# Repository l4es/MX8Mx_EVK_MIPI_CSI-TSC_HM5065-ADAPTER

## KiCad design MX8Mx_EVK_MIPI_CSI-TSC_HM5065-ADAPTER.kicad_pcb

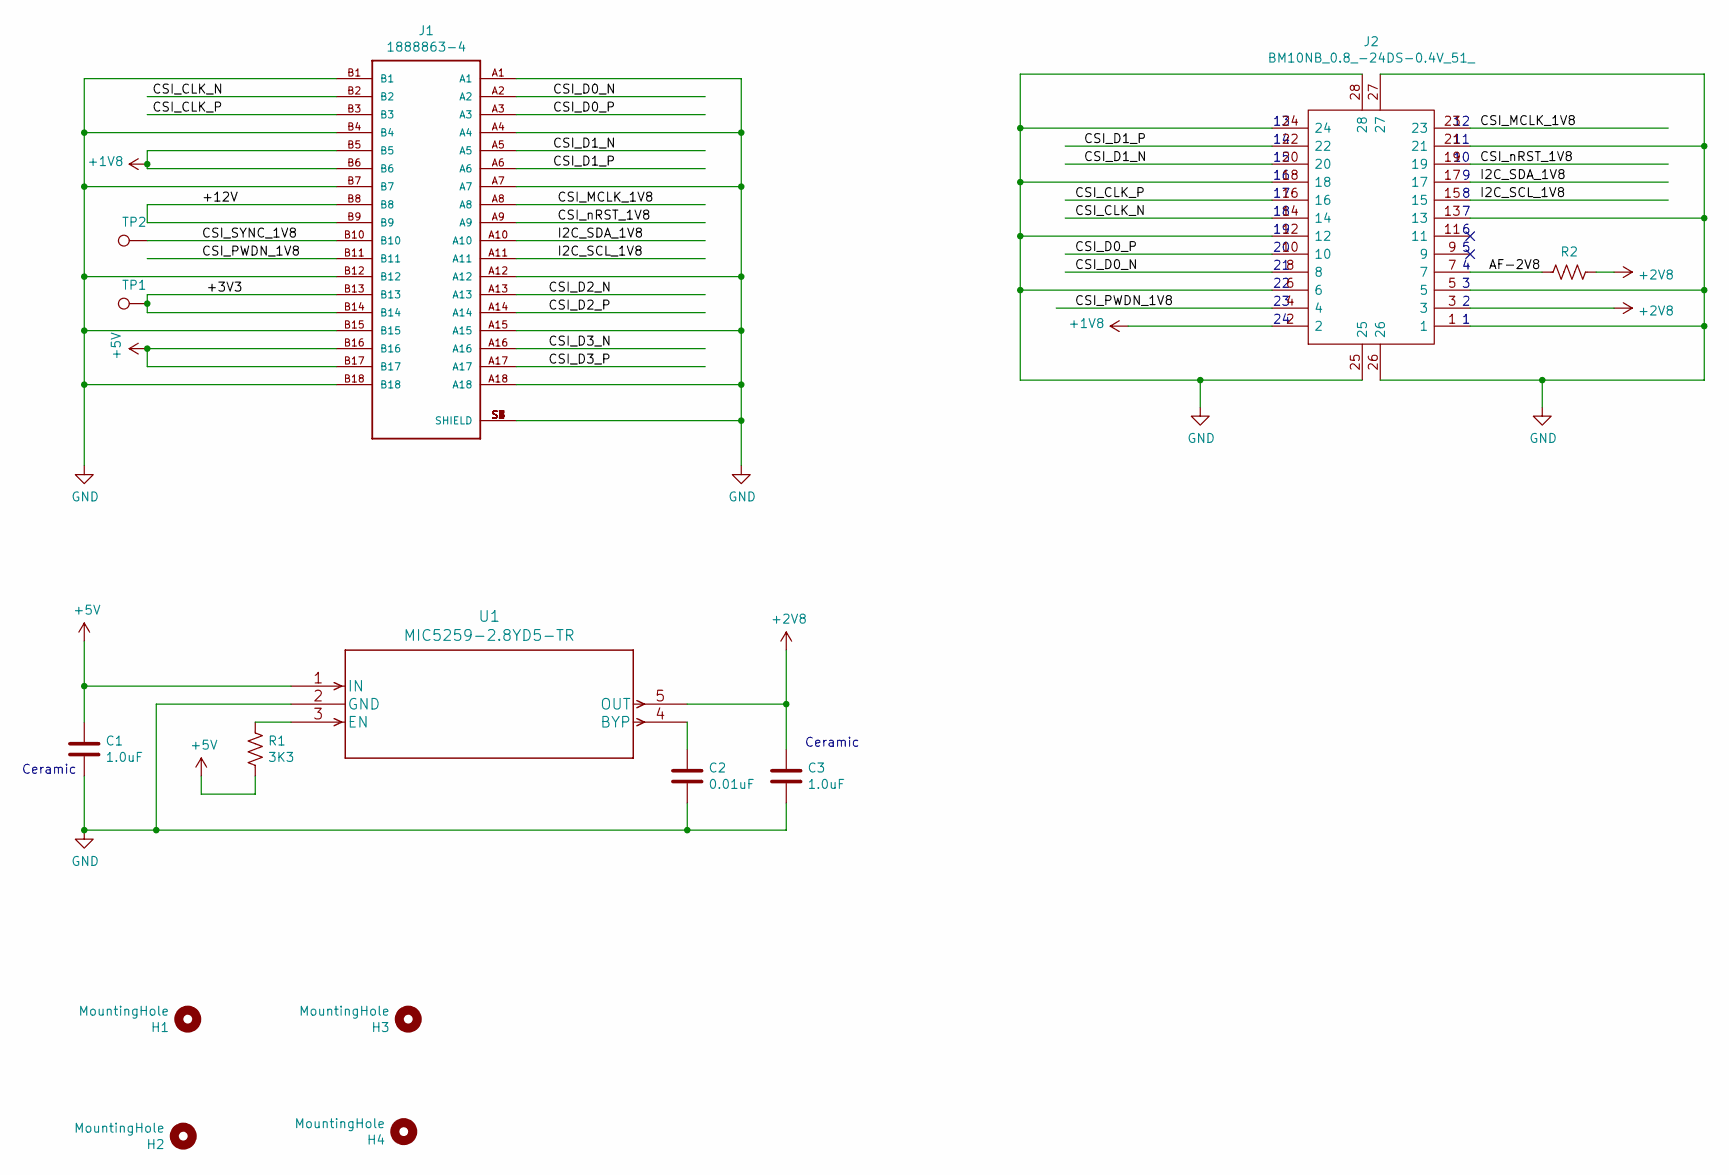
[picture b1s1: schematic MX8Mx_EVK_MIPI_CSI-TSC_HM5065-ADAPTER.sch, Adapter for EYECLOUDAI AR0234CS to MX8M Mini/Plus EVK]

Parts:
C1, C3: 1.0uF; C_0603_1608Metric_Pad1.08x0.95mm_HandSolder
C2: 0.01uF; C_0603_1608Metric_Pad1.08x0.95mm_HandSolder
H1, H2, H3, H4: MountingHole; MountingHole_2.2mm_M2_Pad
J1: 1888863-4; TE_1888863-4
J2: BM10NB_0.8_-24DS-0.4V_51_; BM10NB0824DS04V51; Manufacturer_Part_Number BM10NB(0.8)-24DS-0.4V(51); Mouser Part Number 798-BM10NB0824DS4V51
R1: 3K3; R_0603_1608Metric_Pad0.98x0.95mm_HandSolder
R2: 0; R_0805_2012Metric_Pad1.20x1.40mm_HandSolder
TP1, TP2: TestPoint; TestPoint_Pad_D1.0mm
U1: MIC5259-2.8YD5-TR

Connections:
+1V8: J1.B5, J1.B6, J2.2
+2V8: C3.1, J2.3, R2.2, U1.5 (OUT)
+5V: C1.1, J1.B16, J1.B17, R1.1, U1.1 (IN)
/+3V3: J1.B13, J1.B14, TP1.1
/+12V: J1.B8, J1.B9
/AF-2V8: J2.7, R2.1
/CSI_CLK_N: J1.B2, J2.14
/CSI_CLK_P: J1.B3, J2.16
/CSI_D0_N: J1.A2, J2.8
/CSI_D0_P: J1.A3, J2.10
/CSI_D1_N: J1.A5, J2.20
/CSI_D1_P: J1.A6, J2.22
/CSI_D2_N: J1.A13
/CSI_D2_P: J1.A14
/CSI_D3_N: J1.A16
/CSI_D3_P: J1.A17
/CSI_MCLK_1V8: J1.A8, J2.23
/CSI_PWDN_1V8: J1.B11, J2.4
/CSI_SYNC_1V8: J1.B10, TP2.1
/CSI_nRST_1V8: J1.A9, J2.19
/I2C_SCL_1V8: J1.A11, J2.15
/I2C_SDA_1V8: J1.A10, J2.17
GND: C1.2, C2.2, C3.2, J1.A1, J1.A4, J1.A7, J1.A12, J1.A15, J1.A18, J1.B1, J1.B4, J1.B7, J1.B12, J1.B15, J1.B18, J1.S1 (SHIELD), J1.S2 (SHIELD), J1.S3 (SHIELD), J1.S4 (SHIELD), J1.S5 (SHIELD), J1.S6 (SHIELD), J1.S7 (SHIELD), J1.S8 (SHIELD), J2.1, J2.5, J2.6, J2.12, J2.13, J2.18, J2.21, J2.24, J2.25, J2.26, J2.27, J2.28, U1.2 (GND)
unnamed: C2.1, U1.4 (BYP)
unnamed: R1.2, U1.3 (EN)

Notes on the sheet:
Ceramic

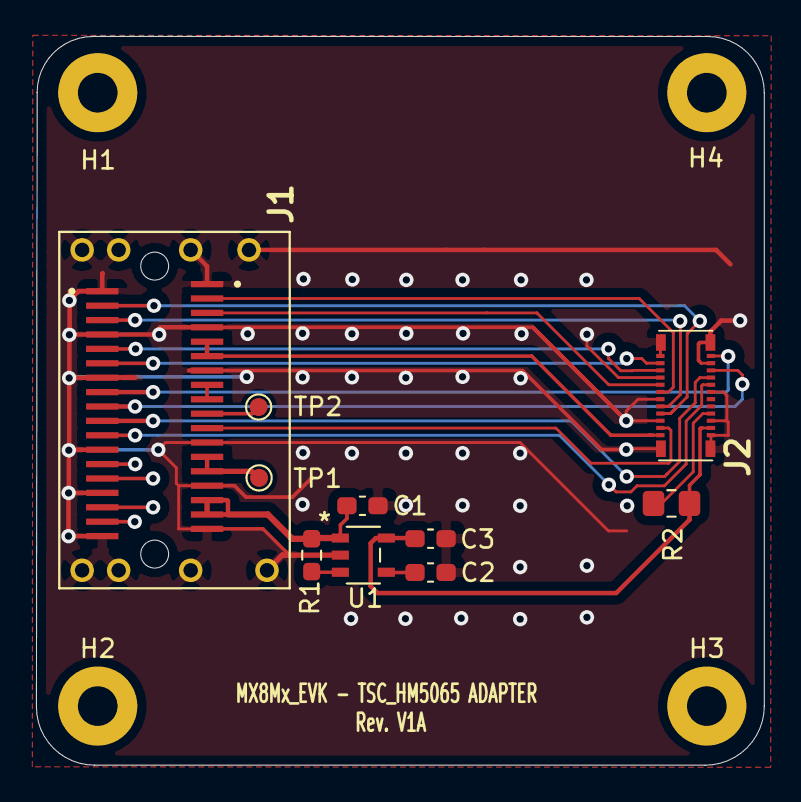
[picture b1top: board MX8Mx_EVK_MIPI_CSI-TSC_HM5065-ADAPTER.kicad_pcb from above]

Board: 2 copper layers, 40.4 x 40.5 mm, 14 parts (0 on the bottom side), 21 nets.

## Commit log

2022-05-06 Add first schematic
2022-05-06 Finish layout
2022-05-07 Add production V1A

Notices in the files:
parts and their libraries:
Copyright 2021 Accelerated Designs. All rights reserved.
